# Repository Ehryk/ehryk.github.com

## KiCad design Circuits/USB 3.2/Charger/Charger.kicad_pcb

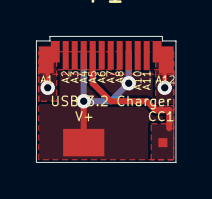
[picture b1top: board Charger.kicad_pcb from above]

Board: 2 copper layers, 7.8 x 7.0 mm, 4 parts (1 on the bottom side), 3 nets.

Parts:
P1: USB_C_Plug; USB_C_3.2
W1: V+; Pad
W2: CC1; Pad_Small
W3: GND; Pad

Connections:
/CC1: P1.A5 (CC), W2.1
/GND: P1.A1 (GND), P1.A12 (GND), P1.B1 (GND), P1.B12 (GND), W3.1
/Vbus: P1.A4 (VBUS), P1.A9 (VBUS), P1.B4 (VBUS), P1.B9 (VBUS), W1.1
